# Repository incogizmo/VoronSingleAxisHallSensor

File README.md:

# Single Axis Hall Sensor for Voron
This is a hall effect sensor based of the existing Voron hall effect sensor for Voron v2.
Designed to be a single axis only and fit within the Y endstop area of V1.8 and be small enough to be flexible for mounting options for X axis.

In this branch the output is Normally Closed. This will provide failsafes if the board / wiring fails, testing needs to be done to ensure accuracy in this configuration.

The comparator in this branch is different to maintain the same PCB layout.

NOTE: THIS IS UNTESTED AND I SUSPECT THERE IS AN ISSUE WITH THE CURRENT SCHEMATIC (SIGNAL ALWAYS SUNK TO GROUND), USE/ORDER AT YOUR OWN RISK

This is designed for use with Voron v1.8 printer: https://github.com/VoronDesign/ http://vorondesign.com/

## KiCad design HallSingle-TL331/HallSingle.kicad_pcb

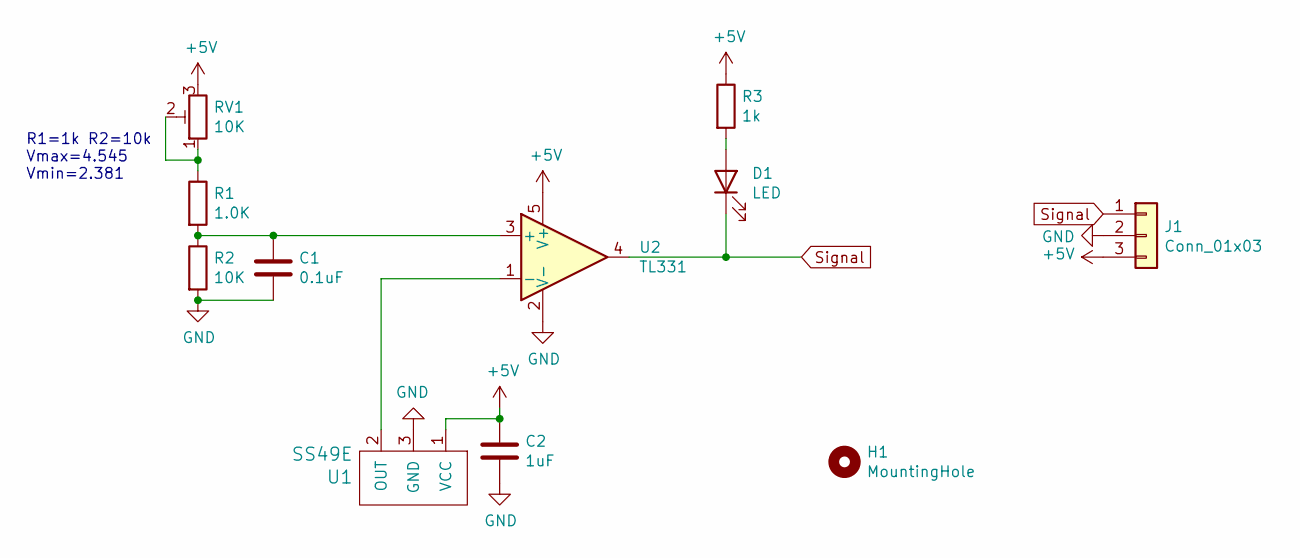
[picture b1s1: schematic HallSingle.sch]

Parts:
C1: 0.1uF; C_0805_2012Metric
C2: 1uF; C_0805_2012Metric
D1: LED; LED_0805_2012Metric
H1: MountingHole; MountingHole_3.2mm_M3
J1: Conn_01x03; JST_XH_B3B-XH-A_1x03_P2.50mm_Vertical
R1: 1.0K; R_0805_2012Metric
R2: 10K; R_0805_2012Metric
R3: 1k; R_0805_2012Metric
RV1: 10K; Potentiometer_3x3
U1: SS49E; SOT-23
U2: TL331; SOT-23-5

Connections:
+5V: C2.1, J1.3, R3.1, RV1.3, U1.1 (VCC), U2.5 (V+)
GND: C1.2, C2.2, J1.2, R2.2, U1.3 (GND), U2.2 (V-)
unnamed: C1.1, R1.2, R2.1, U2.3 (+)
unnamed: D1.2 (A), R3.2
unnamed: R1.1, RV1.1, RV1.2
unnamed: U1.2 (OUT), U2.1 (-)
Signal: D1.1 (K), J1.1, U2.4

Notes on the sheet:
R1=1k R2=10k Vmax=4.545 Vmin=2.381

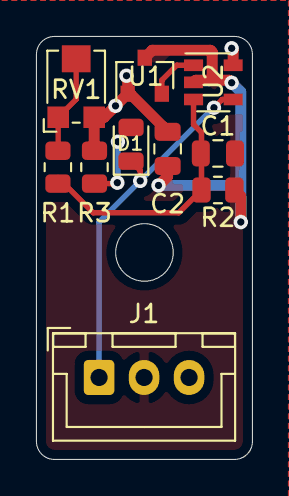
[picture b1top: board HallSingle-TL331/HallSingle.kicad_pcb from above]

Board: 2 copper layers, 12.0 x 23.5 mm, 11 parts (0 on the bottom side), 7 nets.

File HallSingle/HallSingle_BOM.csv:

"Id";"Designator";"Package";"Quantity";"Designation";"Supplier and ref";
1;"H1";"MountingHole_3.2mm_M3";1;"MountingHole";;;
2;"U2";"SOT-23-5";1;"TL331";;;
3;"U1";"SOT-23";1;"SS49E";;;
4;"RV1";"CT6EP103";1;"10K";;;
5;"R3";"R_0805_2012Metric";1;"1k";;;
6;"R2";"R_0805_2012Metric";1;"10K";;;
7;"R1";"R_0805_2012Metric";1;"1.0K";;;
8;"J1";"PinHeader_1x03_P2.54mm_Vertical";1;"Conn_01x03";;;
9;"D1";"LED_0805_2012Metric";1;"LED";;;
10;"C2";"C_0805_2012Metric";1;"1uF";;;
11;"C1";"C_0805_2012Metric";1;"0.1uF";;;

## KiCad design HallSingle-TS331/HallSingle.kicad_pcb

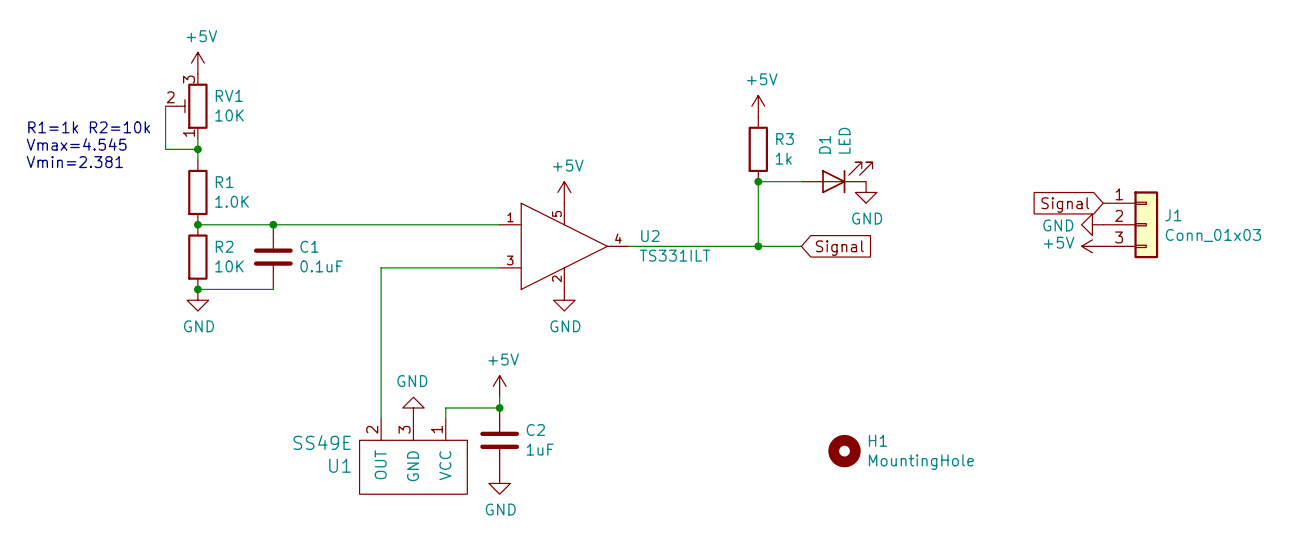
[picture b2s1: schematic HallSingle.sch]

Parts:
C1: 0.1uF; C_0805_2012Metric
C2: 1uF; C_0805_2012Metric
D1: LED; LED_0805_2012Metric
H1: MountingHole; MountingHole_3.2mm_M3
J1: Conn_01x03; PinHeader_1x03_P2.54mm_Vertical
R1: 1.0K; R_0805_2012Metric
R2: 10K; R_0805_2012Metric
R3: 1k; R_0805_2012Metric
RV1: 10K; CT6EP103
U1: SS49E; SOT-23
U2: TS331ILT; SOT-23-5; mouser part number 511-TS331ILT; digikey description IC COMPARATOR SINGLE SOT23-5

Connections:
+5V: C2.1, J1.3, R3.1, RV1.3, U1.1 (VCC), U2.5 (VCC+)
GND: C1.2, C2.2, D1.1 (K), J1.2, R2.2, U1.3 (GND), U2.2 (VCC-)
unnamed: C1.1, R1.2, R2.1, U2.1 (IN+)
unnamed: R1.1, RV1.1, RV1.2
unnamed: U1.2 (OUT), U2.3 (IN-)
Signal: D1.2 (A), J1.1, R3.2, U2.4 (OUT)

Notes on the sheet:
R1=1k R2=10k Vmax=4.545 Vmin=2.381

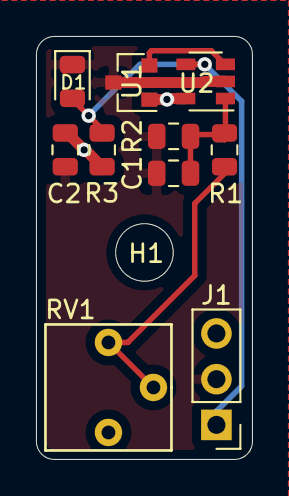
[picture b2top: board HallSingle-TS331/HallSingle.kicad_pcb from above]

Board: 2 copper layers, 12.0 x 23.5 mm, 11 parts (0 on the bottom side), 6 nets.

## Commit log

2020-12-30 initial import
2020-12-30 Added PCB jpeg
2020-12-30 Added Voron Logo and filled missing resistor value
2020-12-30 Reduced total length 1mm to remove interferance with M5 in V1.8 Y mount
2020-12-30 fixed missed trace
2020-12-30 Reduced size due to almost certain interferance from screw heads on v1.8 Y.
2020-12-30 actually reduce the pcb size this time....
2021-01-02 Fixed Mounting hole
2021-01-02 Remove JLC - doesnt fit with required sizing
2021-01-19 merged autosave with prod pcb
2021-01-20 Changed comparator to reverse - also NOTed the led. this is to help with fault tolerance
2021-01-20 Resolved some design rule issues. update jpg
2021-01-20 Update README.md
    added details about being normally
2021-01-21 Corrected wiring to comparator to NC config. Updated header to be same config as SKR - straight through cable required. update revision number
2021-01-21 Updated with revision number. Corrected header orientation. added ibom
2021-01-21 Forgot the gerbers
2021-01-21 removed gerber.zip (incorrect version)
2021-01-21 Gerber file updates
2021-01-21 Added STL's for voron v1.8
2021-01-21 Added STLs for Voron 1.8
2021-01-21 ibom added
2021-01-22 added ibom and other small fixes
2021-01-22 Added config for ts331 and tl331. Also fixes with vias
2021-01-22 removed incorrect bom files
2021-01-22 Fixed TL orientation. ( previously fixed an error that was not an error ) thining is hard sometimes.
2021-01-22 added info to silkscreen
2021-01-22 further fixes and gerbers updated this time
2021-01-31 Added step files.
2021-01-31 added STEP files
2021-01-31 Update README.md
    suspect there is a design issue where the signal will always be sunk to ground
2021-01-31 Tinier components and different LED schematic
2021-02-01 Back to 0805 because it fits
